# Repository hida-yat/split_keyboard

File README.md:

# 分割キーボード
Seeed XIAO RP2040を使用した40キーのロープロファイル分割キーボード

左右の通信はRJ45ケーブルを使用したUART通信で接続

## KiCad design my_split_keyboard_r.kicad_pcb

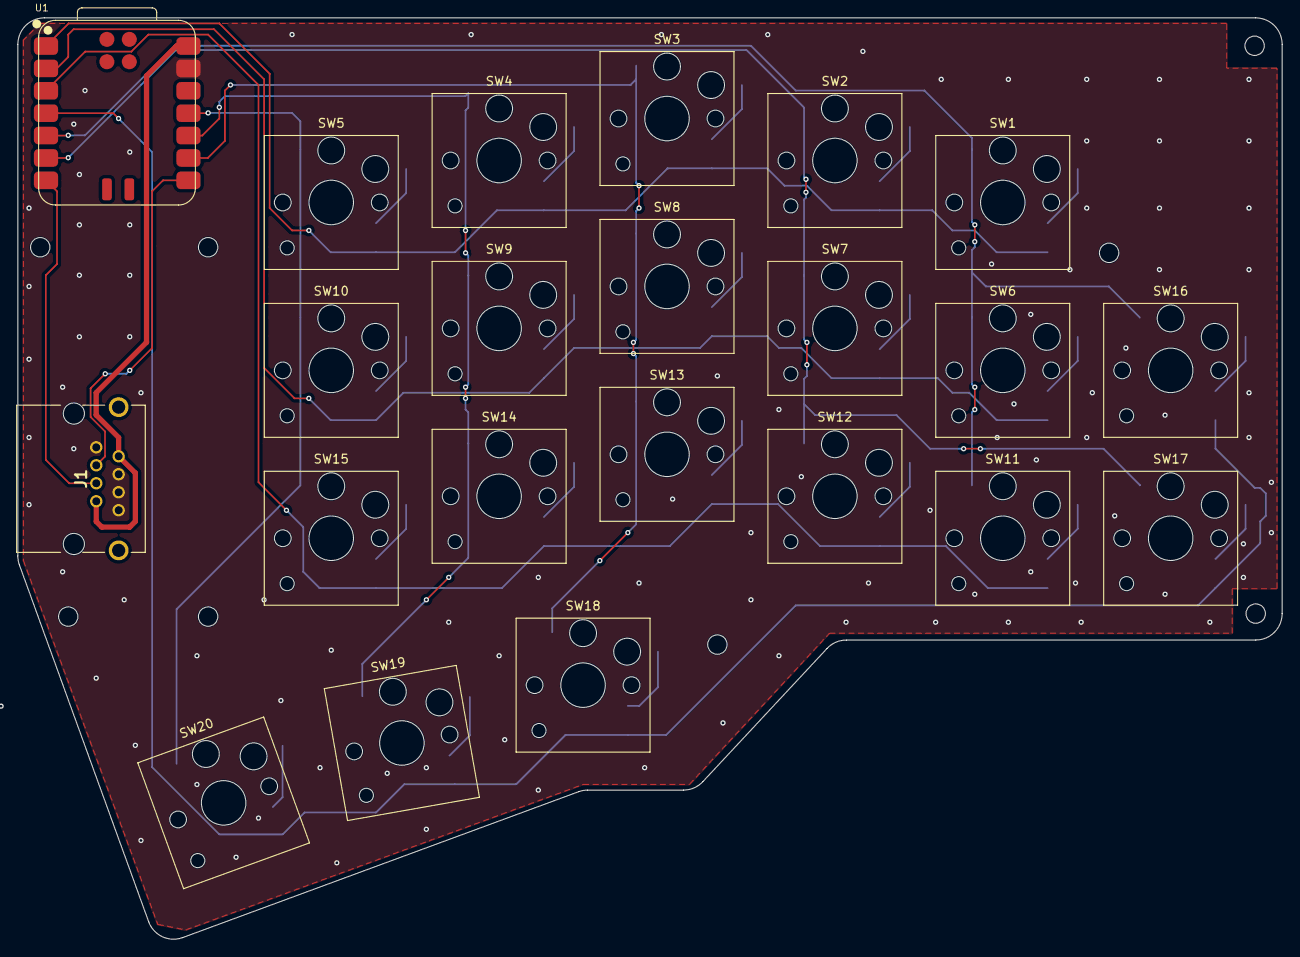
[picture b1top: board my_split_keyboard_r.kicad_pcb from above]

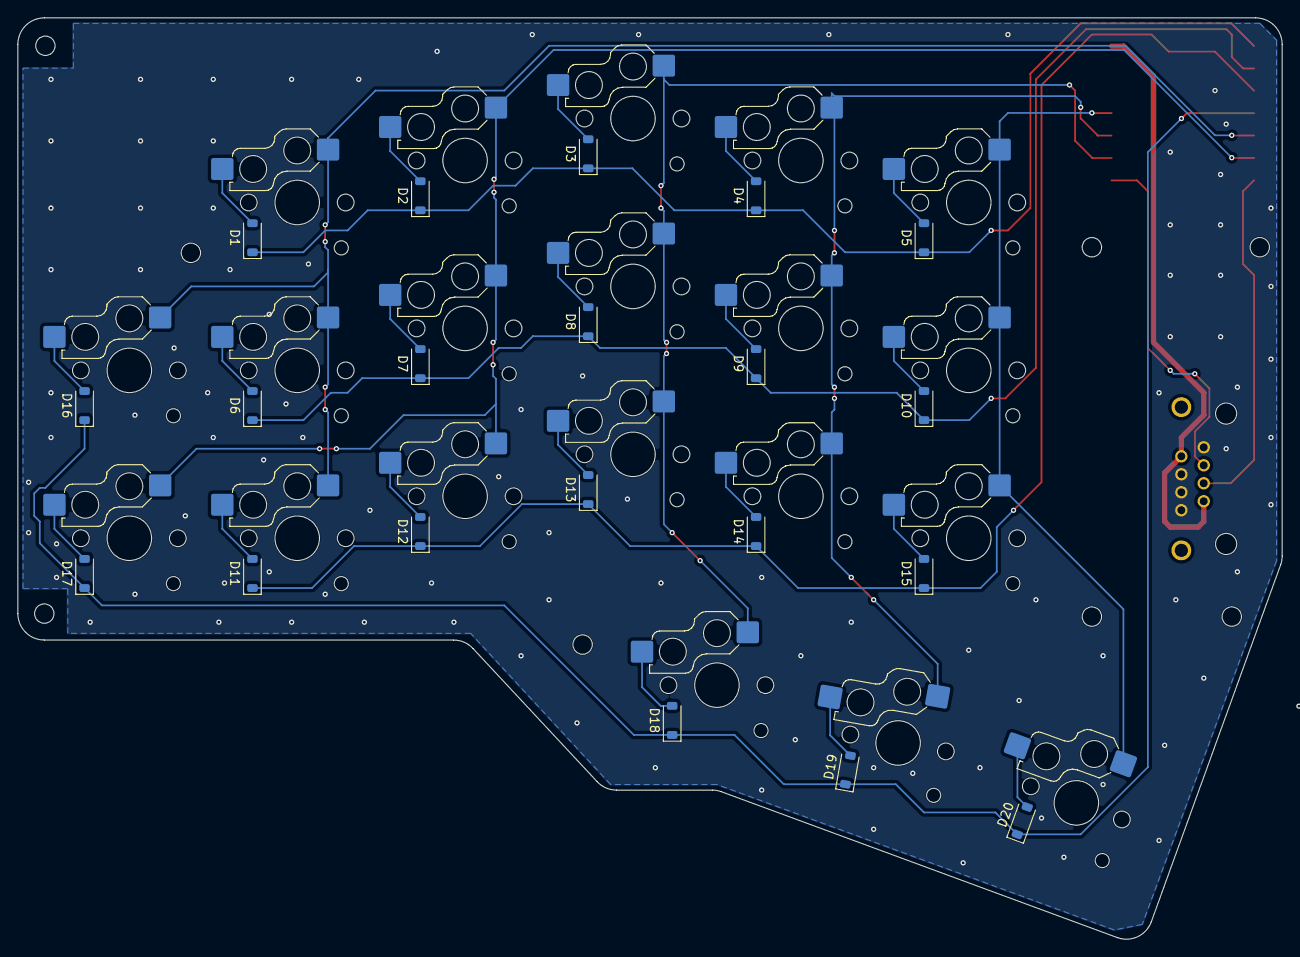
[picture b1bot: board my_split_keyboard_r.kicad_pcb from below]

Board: 2 copper layers, 143.5 x 104.5 mm, 42 parts (20 on the bottom side), 33 nets.

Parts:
D1, D2, D3, D4, D5, D6, D7, D8, D9, D10, D11, D12, D13, D14, D15, D16, D17, D18, D19, D20: D; D_SOD-123
J1: RJ45; 78108P8C
SW1, SW2, SW3, SW4, SW5, SW6, SW7, SW8, SW9, SW10, SW11, SW12, SW13, SW14, SW15, SW16, SW17, SW18, SW19, SW20: SW_Push; SW_Hotswap_Kailh_Choc_V1V2_1.00u
U1: XIAO-RP2040-SMD

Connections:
COL0: SW1.1, SW6.1, SW11.1, SW16.1, U1.5 (SDA_D4)
COL1: SW2.1, SW7.1, SW12.1, SW17.1, U1.6 (SCL_D5)
COL2: SW3.1, SW8.1, SW13.1, SW18.1, U1.9 (D8_SCK)
COL3: SW4.1, SW9.1, SW14.1, SW19.1, U1.10 (D9_MISO)
COL4: SW5.1, SW10.1, SW15.1, SW20.1, U1.11 (D10_MOSI)
GND: J1.1, J1.4, J1.6, J1.8, U1.13 (GND)
unnamed: D1.2 (A), SW1.2
unnamed: D2.2 (A), SW2.2
unnamed: D3.2 (A), SW3.2
unnamed: D4.2 (A), SW4.2
unnamed: D5.2 (A), SW5.2
unnamed: D6.2 (A), SW6.2
unnamed: D7.2 (A), SW7.2
unnamed: D8.2 (A), SW8.2
unnamed: D9.2 (A), SW9.2
unnamed: D10.2 (A), SW10.2
unnamed: D11.2 (A), SW11.2
unnamed: D12.2 (A), SW12.2
unnamed: D13.2 (A), SW13.2
unnamed: D14.2 (A), SW14.2
unnamed: D15.2 (A), SW15.2
unnamed: D16.2 (A), SW16.2
unnamed: D17.2 (A), SW17.2
unnamed: D18.2 (A), SW18.2
unnamed: D19.2 (A), SW19.2
unnamed: D20.2 (A), SW20.2
ROW0: D1.1 (K), D2.1 (K), D3.1 (K), D4.1 (K), D5.1 (K), U1.1 (A0_D0)
ROW1: D6.1 (K), D7.1 (K), D8.1 (K), D9.1 (K), D10.1 (K), U1.2 (A1_D1)
ROW2: D11.1 (K), D12.1 (K), D13.1 (K), D14.1 (K), D15.1 (K), U1.3 (A2_D2)
ROW3: D16.1 (K), D17.1 (K), D18.1 (K), D19.1 (K), D20.1 (K), U1.4 (A3_D3)
RX: J1.3, U1.8 (D7_CSn_RX)
TX: J1.5, U1.7 (TX_D6)
VCC: J1.2, J1.7, U1.14 (5V)

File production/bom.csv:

Designator,Footprint,Quantity,Value,LCSC Part #
"D1, D10, D11, D12, D13, D14, D15, D16, D17, D18, D19, D2, D20, D3, D4, D5, D6, D7, D8, D9",D_SOD-123,20,D,
J1,78108P8C,1,RJ45,
"SW1, SW10, SW11, SW12, SW13, SW14, SW15, SW16, SW17, SW18, SW19, SW2, SW20, SW3, SW4, SW5, SW6, SW7, SW8, SW9",SW_Hotswap_Kailh_Choc_V1V2_1.00u,20,SW_Push,
U1,XIAO-RP2040-SMD,1,~,
